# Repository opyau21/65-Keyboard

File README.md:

# 65% Keyboard Project Files
## Summary
  Creating a 65% Keyboard from scratch without any prior engineering knowledge.

## Next steps:
  * Write Software for ESP32 S3 Mini 1 and STM32

## To Do List:
* PCB: Finished, not yet tested
* Software (In Order)
  1. Keymaps
  2. OLED
  3. Fuel Gauge
  4. Magnetic Encoder
  5. Bluetooth
* Plate
* Foam
* Knob plastics
* Case
  1. Design
  2. Backweight
  3. OLED Screen
* Battery
* Program Software QMK/VIA

## BOM:
| Item # | Reference                                                                                                                                                                                                                                                                                                                                                                                                | Qty | Manufacturer                                                                               | Vendor            | Mfg Part #                                                                                                      | Value              | Description/Value                                                                | Package | Datasheet                                                                                            |
| ------ | -------------------------------------------------------------------------------------------------------------------------------------------------------------------------------------------------------------------------------------------------------------------------------------------------------------------------------------------------------------------------------------------------------- | --- | ------------------------------------------------------------------------------------------ | ----------------- | --------------------------------------------------------------------------------------------------------------- | ------------------ | -------------------------------------------------------------------------------- | ------- | ---------------------------------------------------------------------------------------------------- |
| 1      | C1, C11, C2, C3, C4, C5, C9                                                                                                                                                                                                                                                                                                                                                                              | 6   | Murata Electronics                                                                         | Mouser            | GRM155R71C103KA01J                                                                                              | 100nF              | Multilayer Ceramic Capacitors MLCC - SMD/SMT 0.01 uF 16 VDC 10% 0402 X7R         | 402     | ~                                                                                                    |
| 2      | C10,C15                                                                                                                                                                                                                                                                                                                                                                                                  | 2   | Murata Electronics                                                                         | Mouser            | GRM155R60J475ME47J                                                                                              | 4.7uF              | Multilayer Ceramic Capacitors MLCC - SMD/SMT 4.7 uF 6.3 VDC 20% 0402 X5R         | 402     | ~                                                                                                    |
| 3      | C8,C16                                                                                                                                                                                                                                                                                                                                                                                                   | 2   | Murata Electronics                                                                         | Mouser            | GRM1555C2A101GA01D                                                                                              | 10uF               | Multilayer Ceramic Capacitors MLCC - SMD/SMT 0402 10uF 4VDC 20% X6S AEC-Q200     | 402     | ~                                                                                                    |
| 4      | C14                                                                                                                                                                                                                                                                                                                                                                                                      | 1   | Murata Electronics                                                                         | Mouser            | GRM1555C2A101GA01D                                                                                              | 100pF              | Multilayer Ceramic Capacitors MLCC - SMD/SMT 100 pF 100 VDC 2% 0402 C0G (NP0)    | 402     | ~                                                                                                    |
| 5      | C17                                                                                                                                                                                                                                                                                                                                                                                                      | 1   | Murata Electronics                                                                         | Mouser            | GRM155R61A104KA01J                                                                                              | 0.1uF              | Multilayer Ceramic Capacitors MLCC - SMD/SMT 0.1 uF 10 VDC 10% 0402 X5R          | 402     | https://www.mouser.com/datasheet/2/281/1/GRM155R61A104KA01_02A-1983866.pdf                           |
| 6      | C6, C7                                                                                                                                                                                                                                                                                                                                                                                                   | 2   | Murata Electronics                                                                         | Mouser            | GXT155R60J105KE01D                                                                                              | 1uF                | Multilayer Ceramic Capacitors MLCC - SMD/SMT 0402 6.3VDC 1uF 10% X5R AEC-Q200    | 402     |                                                                                                      |
| 7      | C20,C21,C22,C23,C24,C25,C26,C27,C28,C29,C30,C31,C32,C33,C34,C35,C36,C37,C38,C39,C40,C41,C42,C43,C44,C45,C46,C47,C49,C50,C51,C52,C53,C54,C55,C56,C57,C58,C59,C60,C61,C62,C63,C64,C65,C66,C67,C68,C69,C70,C71,C72,C73,C74,C75,C76,C77,C78,C79,C80,C81,C82,C83,C84,C85,C86,C87                                                                                                                              | 67  | Murata Electronics                                                                         | Mouser            | GCM188R71C104KA37J                                                                                              | 0.1uF              | Multilayer Ceramic Capacitors MLCC - SMD/SMT 0.1 uF 16 VDC 10% 0603 X7R AEC-Q200 | 603     | ~                                                                                                    |
| 8      | D1,D2,D3,D4,D5,D6,D7,D8,D9,D10,D11,D12,D13,D14,D15,D16,D17,D18,D19,D20,D21,D22,D23,D24,D25,D26,D27,D28,D30,D31,D32,D33,D34,D35,D36,D37,D38,D39,D40,D41,D42,D43,D44,D45,D46,D47,D48,D49,D50,D51,D52,D53,D54,D55,D56,D57,D58,D59,D60,D61,D62,D63,D64,D65,D66,D67,D68                                                                                                                                       | 67  |                                                                                            | Adafruit          |                                                                                                                 | D_Small            | Adafruit Accessories 1N4148 SMT SOD-123 Diodes - 100 Pack                        |         | ~                                                                                                    |
| 9      | J1                                                                                                                                                                                                                                                                                                                                                                                                       | 1   |                                                                                            | AliExpress        |                                                                                                                 | Conn_01x02         |                                                                                  |         | ~                                                                                                    |
| 10     | J2                                                                                                                                                                                                                                                                                                                                                                                                       | 1   |                                                                                            | AliExpress        |                                                                                                                 | Conn_01x04         |                                                                                  |         | ~                                                                                                    |
| 11     | J3                                                                                                                                                                                                                                                                                                                                                                                                       | 1   |                                                                                            | AliExpress        |                                                                                                                 | Conn_01x07         |                                                                                  |         | ~                                                                                                    |
| 12     | LED1,LED2,LED3,LED4,LED5,LED6,LED7,LED8,LED9,LED10,LED11,LED12,LED13,LED14,LED15,LED16,LED17,LED18,LED19,LED20,LED21,LED22,LED23,LED24,LED25,LED26,LED27,LED28,LED30,LED31,LED32,LED33,LED34,LED35,LED36,LED37,LED38,LED39,LED40,LED41,LED42,LED43,LED44,LED45,LED46,LED47,LED48,LED49,LED50,LED51,LED52,LED53,LED54,LED55,LED56,LED57,LED58,LED59,LED60,LED61,LED62,LED63,LED64,LED65,LED66,LED67,LED68 | 67  |                                                                                            | AliExpress        |                                                                                                                 | LED_SK6812MINI     |                                                                                  |         | https://cdn-shop.adafruit.com/product-files/2686/SK6812MINI_REV.01-1-2.pdf                           |
| 13     | R1, R11, R12, R17, R3, R5                                                                                                                                                                                                                                                                                                                                                                                | 6   | YAGEO                                                                                      | Mouser            | RC0402JR-7D10KL                                                                                                 | 10k                | Thick Film Resistors - SMD 10 kOhms 62.5 mW 0402 5%                              | 402     | ~                                                                                                    |
| 14     | R6,R7,R8,R9,R10                                                                                                                                                                                                                                                                                                                                                                                          | 5   | YAGEO                                                                                      | Mouser            | [RC0402FR-7D4K7L](https://www.mouser.com/ProductDetail/YAGEO/RC0402FR-7D4K7L?qs=F5EMLAvA7ID7%2FFIVczkChg%3D%3D) | 4.7k               | Thick Film Resistors - SMD 4.7 kOhms 62.5 mW 0402 1%                             | 402     | ~                                                                                                    |
| 15     | R15                                                                                                                                                                                                                                                                                                                                                                                                      | 1   | YAGEO                                                                                      | Mouser            |                                                                                                                 | 1k                 |                                                                                  | 402     | ~                                                                                                    |
| 16     | R16                                                                                                                                                                                                                                                                                                                                                                                                      | 1   | YAGEO                                                                                      | Mouser            |                                                                                                                 | 750                |                                                                                  | 402     | ~                                                                                                    |
| 17     | S1,S2,S3,S4,S5,S6,S7,S8,S9,S10,S11,S12,S13,S14,S16,S17,S18,S19,S20,S21,S22,S23,S24,S25,S26,S27,S31,S32,S33,S34,S35,S36,S37,S38,S39,S40,S41,S42,S43,S44,S45,S46,S47,S48,S49,S50,S51,S52,S53,S54,S56,S57,S61,S64,S65,S66,S71,S72                                                                                                                                                                           | 58  |                                                                                            | Cannonkeys        |                                                                                                                 | Keyswitch          | Kailh MX Hotswap Sockets - 110 Pack                                              |         | ~                                                                                                    |
| 18     | S15,S28                                                                                                                                                                                                                                                                                                                                                                                                  | 2   |                                                                                            |                   |                                                                                                                 | Keyswitch          |                                                                                  |         | ~                                                                                                    |
| 19     | S30,S55                                                                                                                                                                                                                                                                                                                                                                                                  | 2   |                                                                                            |                   |                                                                                                                 | Keyswitch          |                                                                                  |         | ~                                                                                                    |
| 20     | S58,S59,S60,S62,S63                                                                                                                                                                                                                                                                                                                                                                                      | 5   |                                                                                            |                   |                                                                                                                 | Keyswitch          |                                                                                  |         | ~                                                                                                    |
| 21     | S67                                                                                                                                                                                                                                                                                                                                                                                                      | 1   |                                                                                            | Divinikey         |                                                                                                                 | MX_stab            | TX Stabilizers                                                                   |         |                                                                                                      |
| 22     | S68,S69                                                                                                                                                                                                                                                                                                                                                                                                  | 2   |                                                                                            |                   |                                                                                                                 | MX_stab            |                                                                                  |         |                                                                                                      |
| 23     | S70                                                                                                                                                                                                                                                                                                                                                                                                      | 1   |                                                                                            |                   |                                                                                                                 | MX_stab            |                                                                                  |         |                                                                                                      |
| 24     | SW1,SW2                                                                                                                                                                                                                                                                                                                                                                                                  | 2   | E-Switch                                                                                   | Mouser            | TL3342F450QG                                                                                                    | SW_Push            | Tactile Switches 50mA 12VDC Silver Gull Wing                                     |         | ~                                                                                                    |
| 25     | U1                                                                                                                                                                                                                                                                                                                                                                                                       | 1   | [Analog Devices / Maxim Integrated](https://www.mouser.com/manufacturer/maxim-integrated/) | Mouser            | MAX17048G+T10                                                                                                   | MAX17048G_T10      | Battery Management 3 A 1-Cell/2-Cell Fuel Gauge with ModelGauge                  |         |                                                                                                      |
| 26     | U2                                                                                                                                                                                                                                                                                                                                                                                                       | 1   | Semtech                                                                                    | Mouser            | SRV05-4.TCT                                                                                                     | SRV05-4            | ESD Protection Diodes / TVS Diodes RAILCLAMP 4-LINE 5V 3K LFREE                  |         | http://www.onsemi.com/pub/Collateral/SRV05-4-D.PDF                                                   |
| 27     | U3                                                                                                                                                                                                                                                                                                                                                                                                       | 1   | Azoteq                                                                                     | Mouser            | IQS6243200DNR                                                                                                   | IQS624-3200-DNR    | Board Mount Motion & Position Sensors 2 x Capacitive, Hall rotation              |         |                                                                                                      |
| 28     | U4                                                                                                                                                                                                                                                                                                                                                                                                       | 1   | EspressIf                                                                                  | Mouser            | ESP32-S3-MINI-1-N8                                                                                              | ESP32-S3-MINI-1-N8 | Multiprotocol Modules SMD module, ESP32-S3FN8, 8 MB SPI flash, PCB antenna       |         | https://www.espressif.com/sites/default/files/documentation/esp32-s3-mini-1_mini-1u_datasheet_en.pdf |
| 29     | U5                                                                                                                                                                                                                                                                                                                                                                                                       | 1   |                                                                                            | Mouser            | BQ25185DLHR                                                                                                     | BQ25185DLHR        |                                                                                  |         |                                                                                                      |
| 30     | U6                                                                                                                                                                                                                                                                                                                                                                                                       | 1   | STMicroelectronics                                                                         | Mouser            | STM32F103RET6TR                                                                                                 | STM32F103RETx      | ARM Microcontrollers - MCU 32BIT Cortex M3 H/D Performance LINE                  |         | https://www.st.com/resource/en/datasheet/stm32f103re.pdf                                             |
| 31     | U7                                                                                                                                                                                                                                                                                                                                                                                                       | 1   | UMW                                                                                        | Digikey           | AMS1117-3.3                                                                                                     | AMS1117-3.3        | 3.3V LDO Regulator                                                               |         |                                                                                                      |
| 32     | F1                                                                                                                                                                                                                                                                                                                                                                                                       | 1   | Bourns                                                                                     | Mouser            | MF-FSMF050X-2                                                                                                   | MF-FSMF050X-2      | Resettable Fuses - PPTC 6V .5A-HD 40A MAX                                        |         |                                                                                                      |
| 33     |                                                                                                                                                                                                                                                                                                                                                                                                          | 1   |                                                                                            | Amazon/AliExpress |                                                                                                                 | 5000 mah           | 5000 mah Lithium Ion Recharable Battery                                          |         |                                                                                                      |
| 34     |                                                                                                                                                                                                                                                                                                                                                                                                          | 1   |                                                                                            | AliExpress        |                                                                                                                 | 01x07 JST PH Wire  | 01x07 JST PH Wire                                                                |         |                                                                                                      |
| 35     |                                                                                                                                                                                                                                                                                                                                                                                                          | 1   | aio3                                                                                       | Cannonkeys        |                                                                                                                 |                    | Unified Daughterboard                                                            |         |                                                                                                      |
| 36     |                                                                                                                                                                                                                                                                                                                                                                                                          | 1   | Waveshare                                                                                  | Amazon            |                                                                                                                 | 128 x 128          | 1.5 inch 128 x 128 RGB OLED Screen                                               |         |                                                                                                      |
| 37     |                                                                                                                                                                                                                                                                                                                                                                                                          | 1   | Logitech                                                                                   | AliExpress        |                                                                                                                 |                    | Logitech MX Master 3s Side Scroll Component                                      |         |                                                                                                      |

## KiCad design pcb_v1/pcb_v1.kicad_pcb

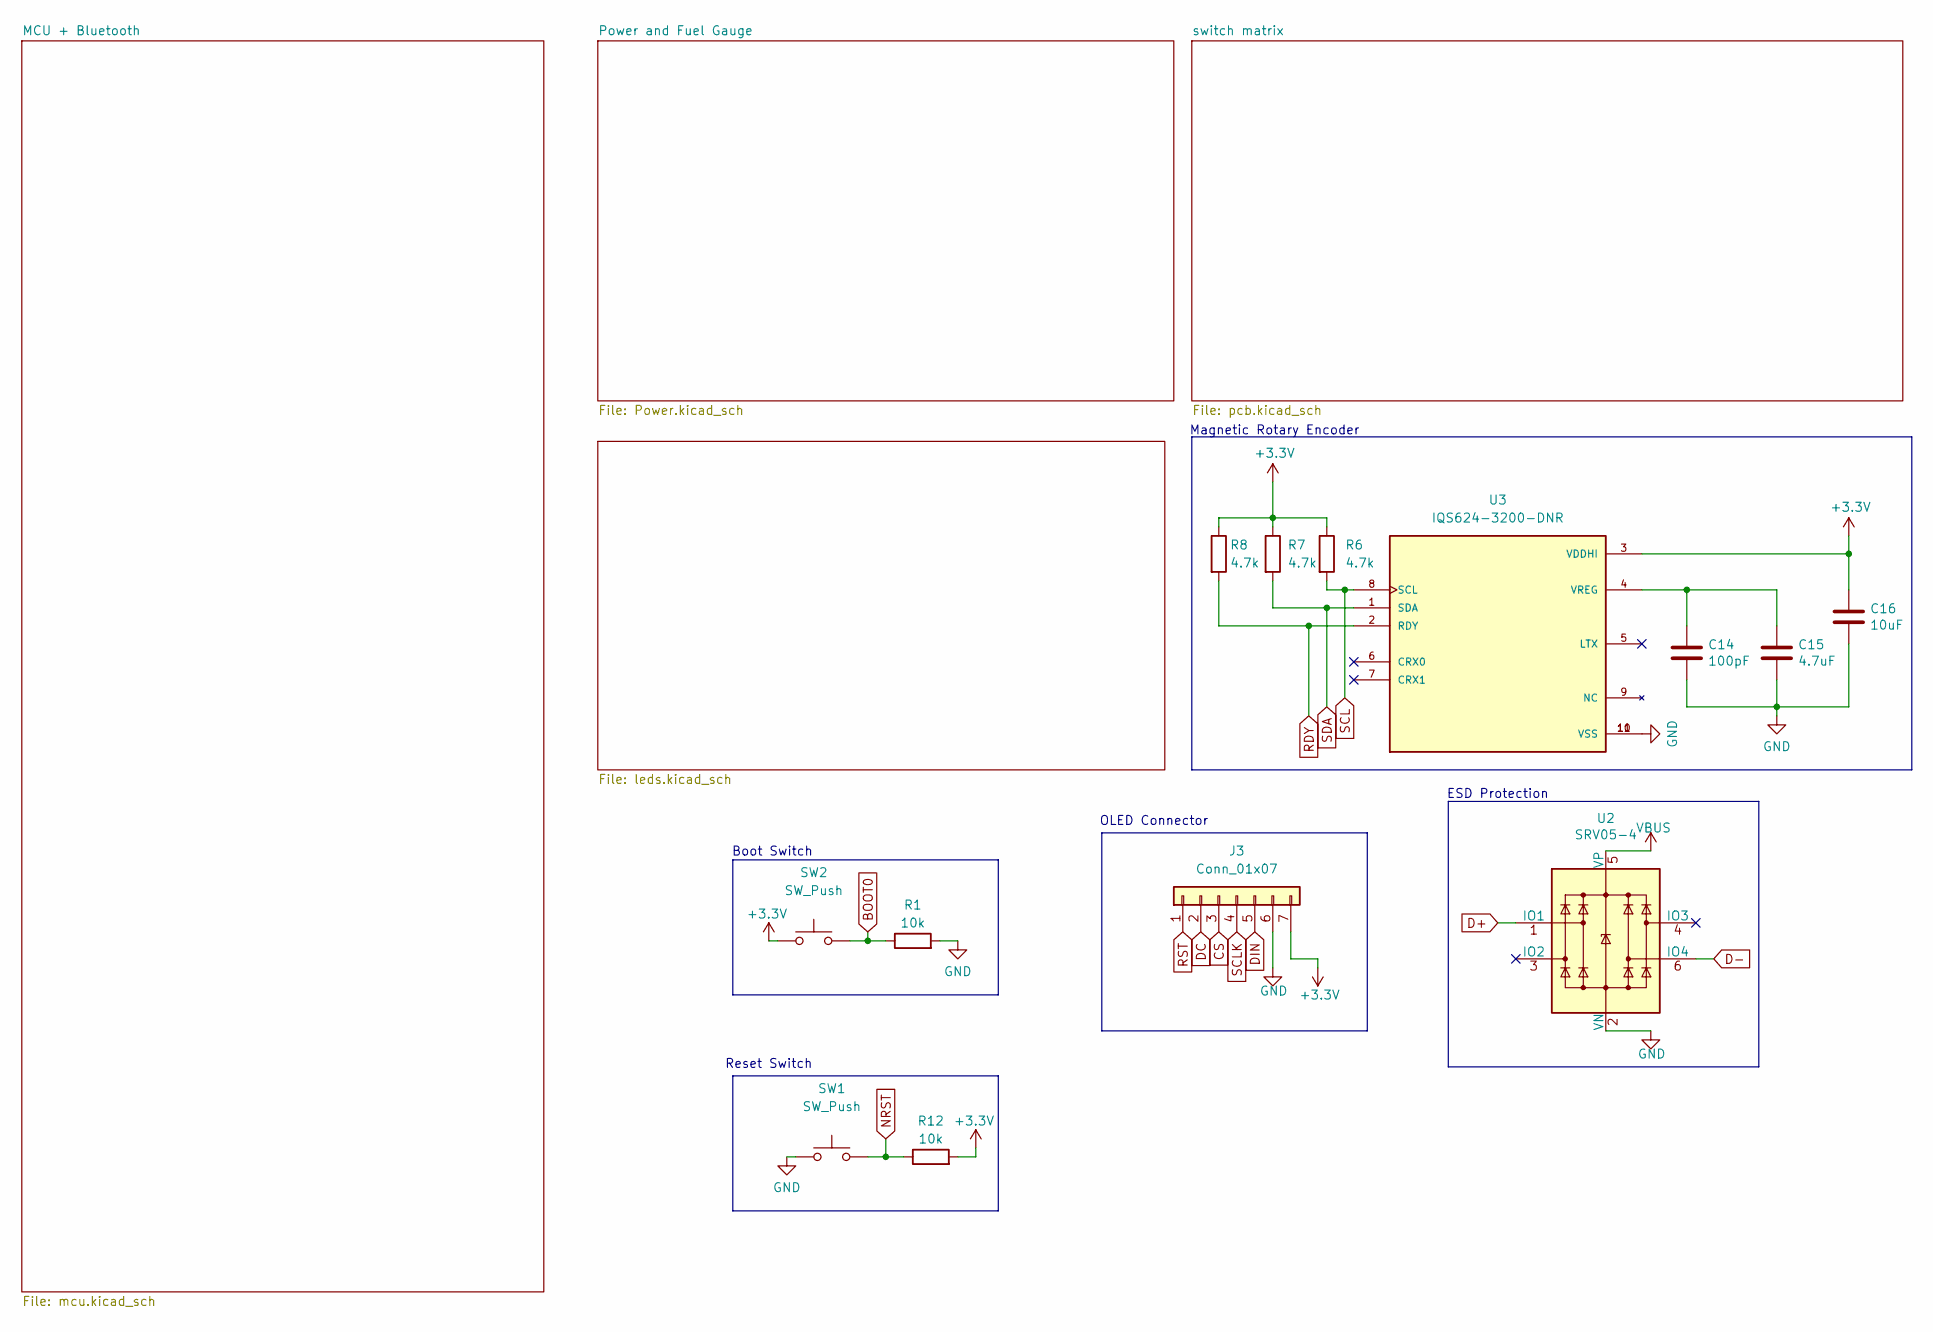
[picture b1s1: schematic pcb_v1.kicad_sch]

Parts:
C14: 100pF; CAPC1005X55N; LCSC Part # C49678
C15: 4.7uF; CAPC1005X55N; LCSC Part # C49678
C16: 10uF; CAPC1005X55N; LCSC Part # C49678
J3: Conn_01x07; JST_PH_S7B-PH-SM4-TB_1x07-1MP_P2.00mm_Horizontal
R1, R12: 10k; RESC1005X40N
R6, R7, R8: 4.7k; RESC1005X40N
SW1, SW2: SW_Push; Button_TL3342
U2: SRV05-4; SOT-23-6; LCSC Part # C85364
U3: IQS624-3200-DNR; SON50P300X300X80-11N; PARTREV 2.04

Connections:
+3.3V: C16.1, J3.7, R6.1, R7.1, R8.1, R12.2, SW2.1, U3.3 (VDDHI); also elsewhere on the board
BOOT0: R1.1, SW2.2; also elsewhere on the board
CS: J3.3; also elsewhere on the board
D+: U2.1 (IO1); also elsewhere on the board
D-: U2.6 (IO4); also elsewhere on the board
DC: J3.2; also elsewhere on the board
DIN: J3.5; also elsewhere on the board
GND: C14.2, C15.2, C16.2, J3.6, R1.2, SW1.1, U2.2 (VN), U3.10 (VSS), U3.11 (VSS); also elsewhere on the board
NRST: R12.1, SW1.2; also elsewhere on the board
unnamed: C14.1, C15.1, U3.4 (VREG)
RDY: R8.2, U3.2 (RDY); also elsewhere on the board
RST: J3.1; also elsewhere on the board
SCL: R6.2, U3.8 (SCL); also elsewhere on the board
SCLK: J3.4; also elsewhere on the board
SDA: R7.2, U3.1 (SDA); also elsewhere on the board
VBUS: U2.5 (VP); also elsewhere on the board

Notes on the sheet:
OLED Connector
Boot Switch
ESD Protection
Magnetic Rotary Encoder
Reset Switch

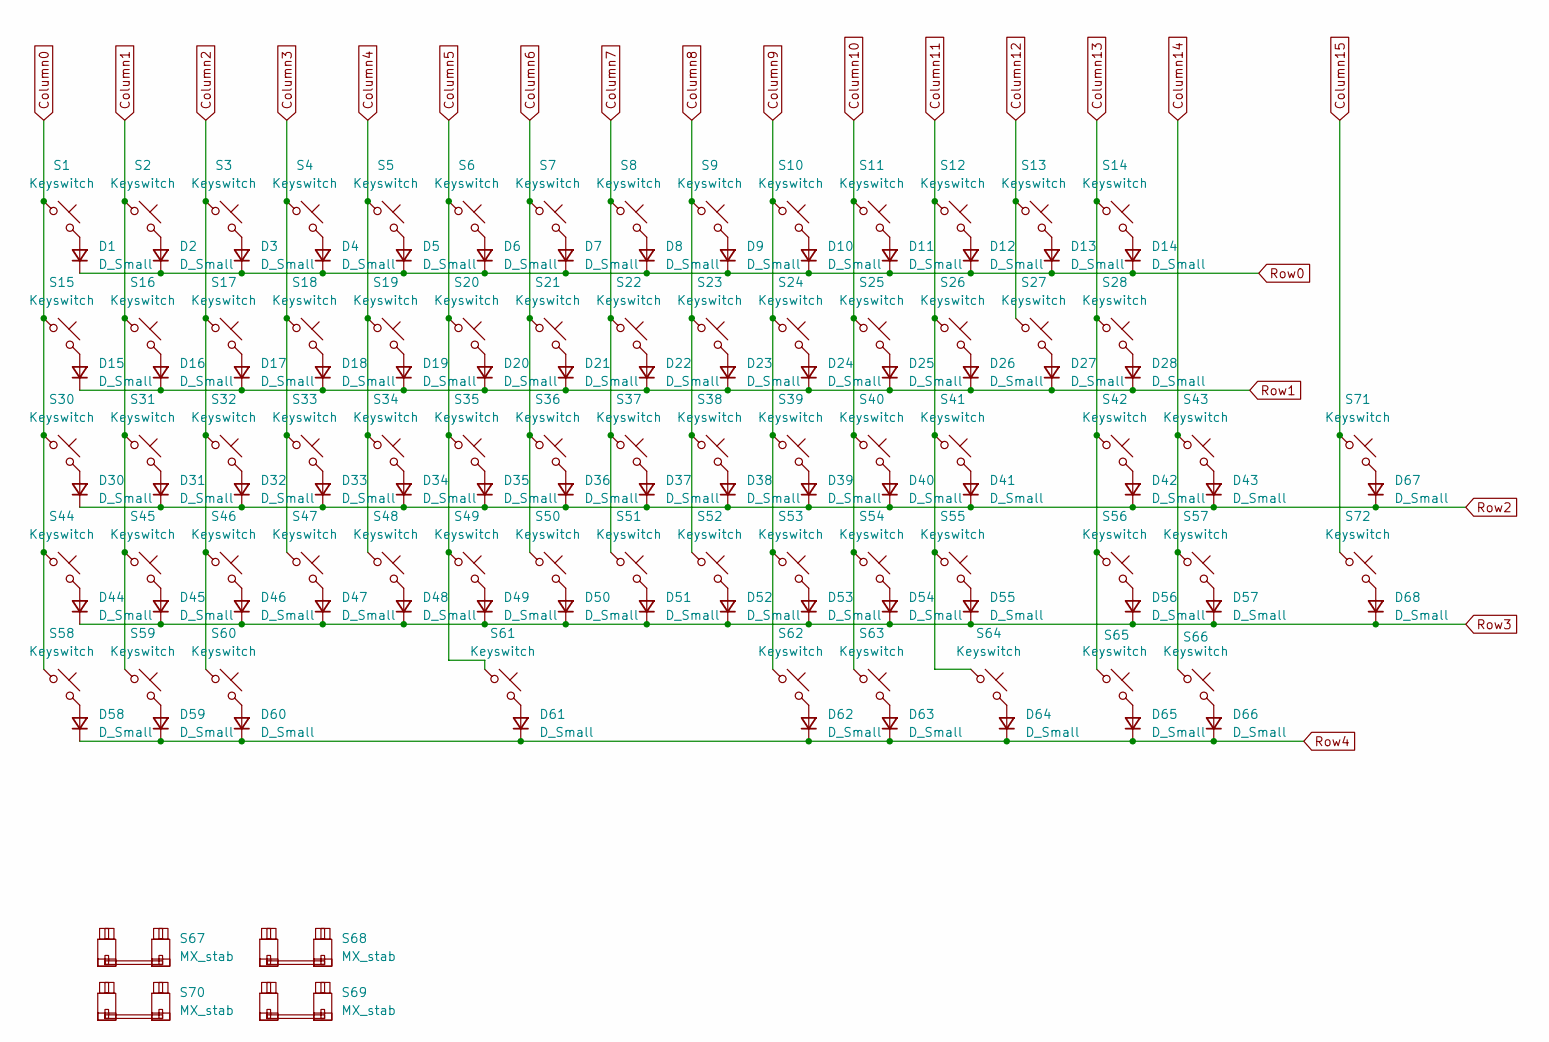
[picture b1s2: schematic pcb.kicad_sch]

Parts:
D1, D2, D3, D4, D5, D6, D7, D8, D9, D10, D11, D12, D13, D14, D15, D16, D17, D18, D19, D20, D21, D22, D23, D24, D25, D26, D27, D28, D30, D31, D32, D33, D34, D35, D36, D37, D38, D39, D40, D41, D42, D43, D44, D45, D46, D47, D48, D49, D50, D51, D52, D53, D54, D55, D56, D57, D58, D59, D60, D61, D62, D63, D64, D65, D66, D67, D68: D_Small; Diode_SOD-123
S1, S2, S3, S4, S5, S6, S7, S8, S9, S10, S11, S12, S13, S14, S16, S17, S18, S19, S20, S21, S22, S23, S24, S25, S26, S27, S31, S32, S33, S34, S35, S36, S37, S38, S39, S40, S41, S42, S43, S44, S45, S46, S47, S48, S49, S50, S51, S52, S53, S54, S56, S57, S61, S64, S65, S66, S71, S72: Keyswitch; SW_MX_HS_CPG151101S11_1u
S15, S28: Keyswitch; SW_MX_HS_CPG151101S11_1.5u
S30, S55: Keyswitch; SW_MX_HS_CPG151101S11_1.75u
S58, S59, S60, S62, S63: Keyswitch; SW_MX_HS_CPG151101S11_1.25u
S67: MX_stab; STAB_MX_P_2u
S68, S69: MX_stab; STAB_MX_2.25u
S70: MX_stab; STAB_MX_P_6.25u

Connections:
Column0: S1.1, S15.1, S30.1, S44.1, S58.1; also elsewhere on the board
Column1: S2.1, S16.1, S31.1, S45.1, S59.1; also elsewhere on the board
Column2: S3.1, S17.1, S32.1, S46.1, S60.1; also elsewhere on the board
Column3: S4.1, S18.1, S33.1, S47.1; also elsewhere on the board
Column4: S5.1, S19.1, S34.1, S48.1; also elsewhere on the board
Column5: S6.1, S20.1, S35.1, S49.1, S61.1; also elsewhere on the board
Column6: S7.1, S21.1, S36.1, S50.1; also elsewhere on the board
Column7: S8.1, S22.1, S37.1, S51.1; also elsewhere on the board
Column8: S9.1, S23.1, S38.1, S52.1; also elsewhere on the board
Column9: S10.1, S24.1, S39.1, S53.1, S62.1; also elsewhere on the board
Column10: S11.1, S25.1, S40.1, S54.1, S63.1; also elsewhere on the board
Column11: S12.1, S26.1, S41.1, S55.1, S64.1; also elsewhere on the board
Column12: S13.1, S27.1; also elsewhere on the board
Column13: S14.1, S28.1, S42.1, S56.1, S65.1; also elsewhere on the board
Column14: S43.1, S57.1, S66.1; also elsewhere on the board
Column15: S71.1, S72.1; also elsewhere on the board
unnamed: D1.2 (A), S1.2
unnamed: D2.2 (A), S2.2
unnamed: D3.2 (A), S3.2
unnamed: D4.2 (A), S4.2
unnamed: D5.2 (A), S5.2
unnamed: D6.2 (A), S6.2
unnamed: D7.2 (A), S7.2
unnamed: D8.2 (A), S8.2
unnamed: D9.2 (A), S9.2
unnamed: D10.2 (A), S10.2
unnamed: D11.2 (A), S11.2
unnamed: D12.2 (A), S12.2
unnamed: D13.2 (A), S13.2
unnamed: D14.2 (A), S14.2
unnamed: D15.2 (A), S15.2
unnamed: D16.2 (A), S16.2
unnamed: D17.2 (A), S17.2
unnamed: D18.2 (A), S18.2
unnamed: D19.2 (A), S19.2
unnamed: D20.2 (A), S20.2
unnamed: D21.2 (A), S21.2
unnamed: D22.2 (A), S22.2
unnamed: D23.2 (A), S23.2
unnamed: D24.2 (A), S24.2
unnamed: D25.2 (A), S25.2
unnamed: D26.2 (A), S26.2
unnamed: D27.2 (A), S27.2
unnamed: D28.2 (A), S28.2
unnamed: D30.2 (A), S30.2
unnamed: D31.2 (A), S31.2
unnamed: D32.2 (A), S32.2
unnamed: D33.2 (A), S33.2
unnamed: D34.2 (A), S34.2
unnamed: D35.2 (A), S35.2
unnamed: D36.2 (A), S36.2
unnamed: D37.2 (A), S37.2
unnamed: D38.2 (A), S38.2
unnamed: D39.2 (A), S39.2
unnamed: D40.2 (A), S40.2
unnamed: D41.2 (A), S41.2
unnamed: D42.2 (A), S42.2
unnamed: D43.2 (A), S43.2
unnamed: D44.2 (A), S44.2
unnamed: D45.2 (A), S45.2
unnamed: D46.2 (A), S46.2
unnamed: D47.2 (A), S47.2
unnamed: D48.2 (A), S48.2
unnamed: D49.2 (A), S49.2
unnamed: D50.2 (A), S50.2
unnamed: D51.2 (A), S51.2
unnamed: D52.2 (A), S52.2
unnamed: D53.2 (A), S53.2
unnamed: D54.2 (A), S54.2
unnamed: D55.2 (A), S55.2
unnamed: D56.2 (A), S56.2
unnamed: D57.2 (A), S57.2
unnamed: D58.2 (A), S58.2
unnamed: D59.2 (A), S59.2
unnamed: D60.2 (A), S60.2
unnamed: D61.2 (A), S61.2
unnamed: D62.2 (A), S62.2
unnamed: D63.2 (A), S63.2
unnamed: D64.2 (A), S64.2
unnamed: D65.2 (A), S65.2
unnamed: D66.2 (A), S66.2
unnamed: D67.2 (A), S71.2
unnamed: D68.2 (A), S72.2
Row0: D1.1 (K), D2.1 (K), D3.1 (K), D4.1 (K), D5.1 (K), D6.1 (K), D7.1 (K), D8.1 (K), D9.1 (K), D10.1 (K), D11.1 (K), D12.1 (K), D13.1 (K), D14.1 (K); also elsewhere on the board
Row1: D15.1 (K), D16.1 (K), D17.1 (K), D18.1 (K), D19.1 (K), D20.1 (K), D21.1 (K), D22.1 (K), D23.1 (K), D24.1 (K), D25.1 (K), D26.1 (K), D27.1 (K), D28.1 (K); also elsewhere on the board
Row2: D30.1 (K), D31.1 (K), D32.1 (K), D33.1 (K), D34.1 (K), D35.1 (K), D36.1 (K), D37.1 (K), D38.1 (K), D39.1 (K), D40.1 (K), D41.1 (K), D42.1 (K), D43.1 (K), D67.1 (K); also elsewhere on the board
Row3: D44.1 (K), D45.1 (K), D46.1 (K), D47.1 (K), D48.1 (K), D49.1 (K), D50.1 (K), D51.1 (K), D52.1 (K), D53.1 (K), D54.1 (K), D55.1 (K), D56.1 (K), D57.1 (K), D68.1 (K); also elsewhere on the board
Row4: D58.1 (K), D59.1 (K), D60.1 (K), D61.1 (K), D62.1 (K), D63.1 (K), D64.1 (K), D65.1 (K), D66.1 (K); also elsewhere on the board

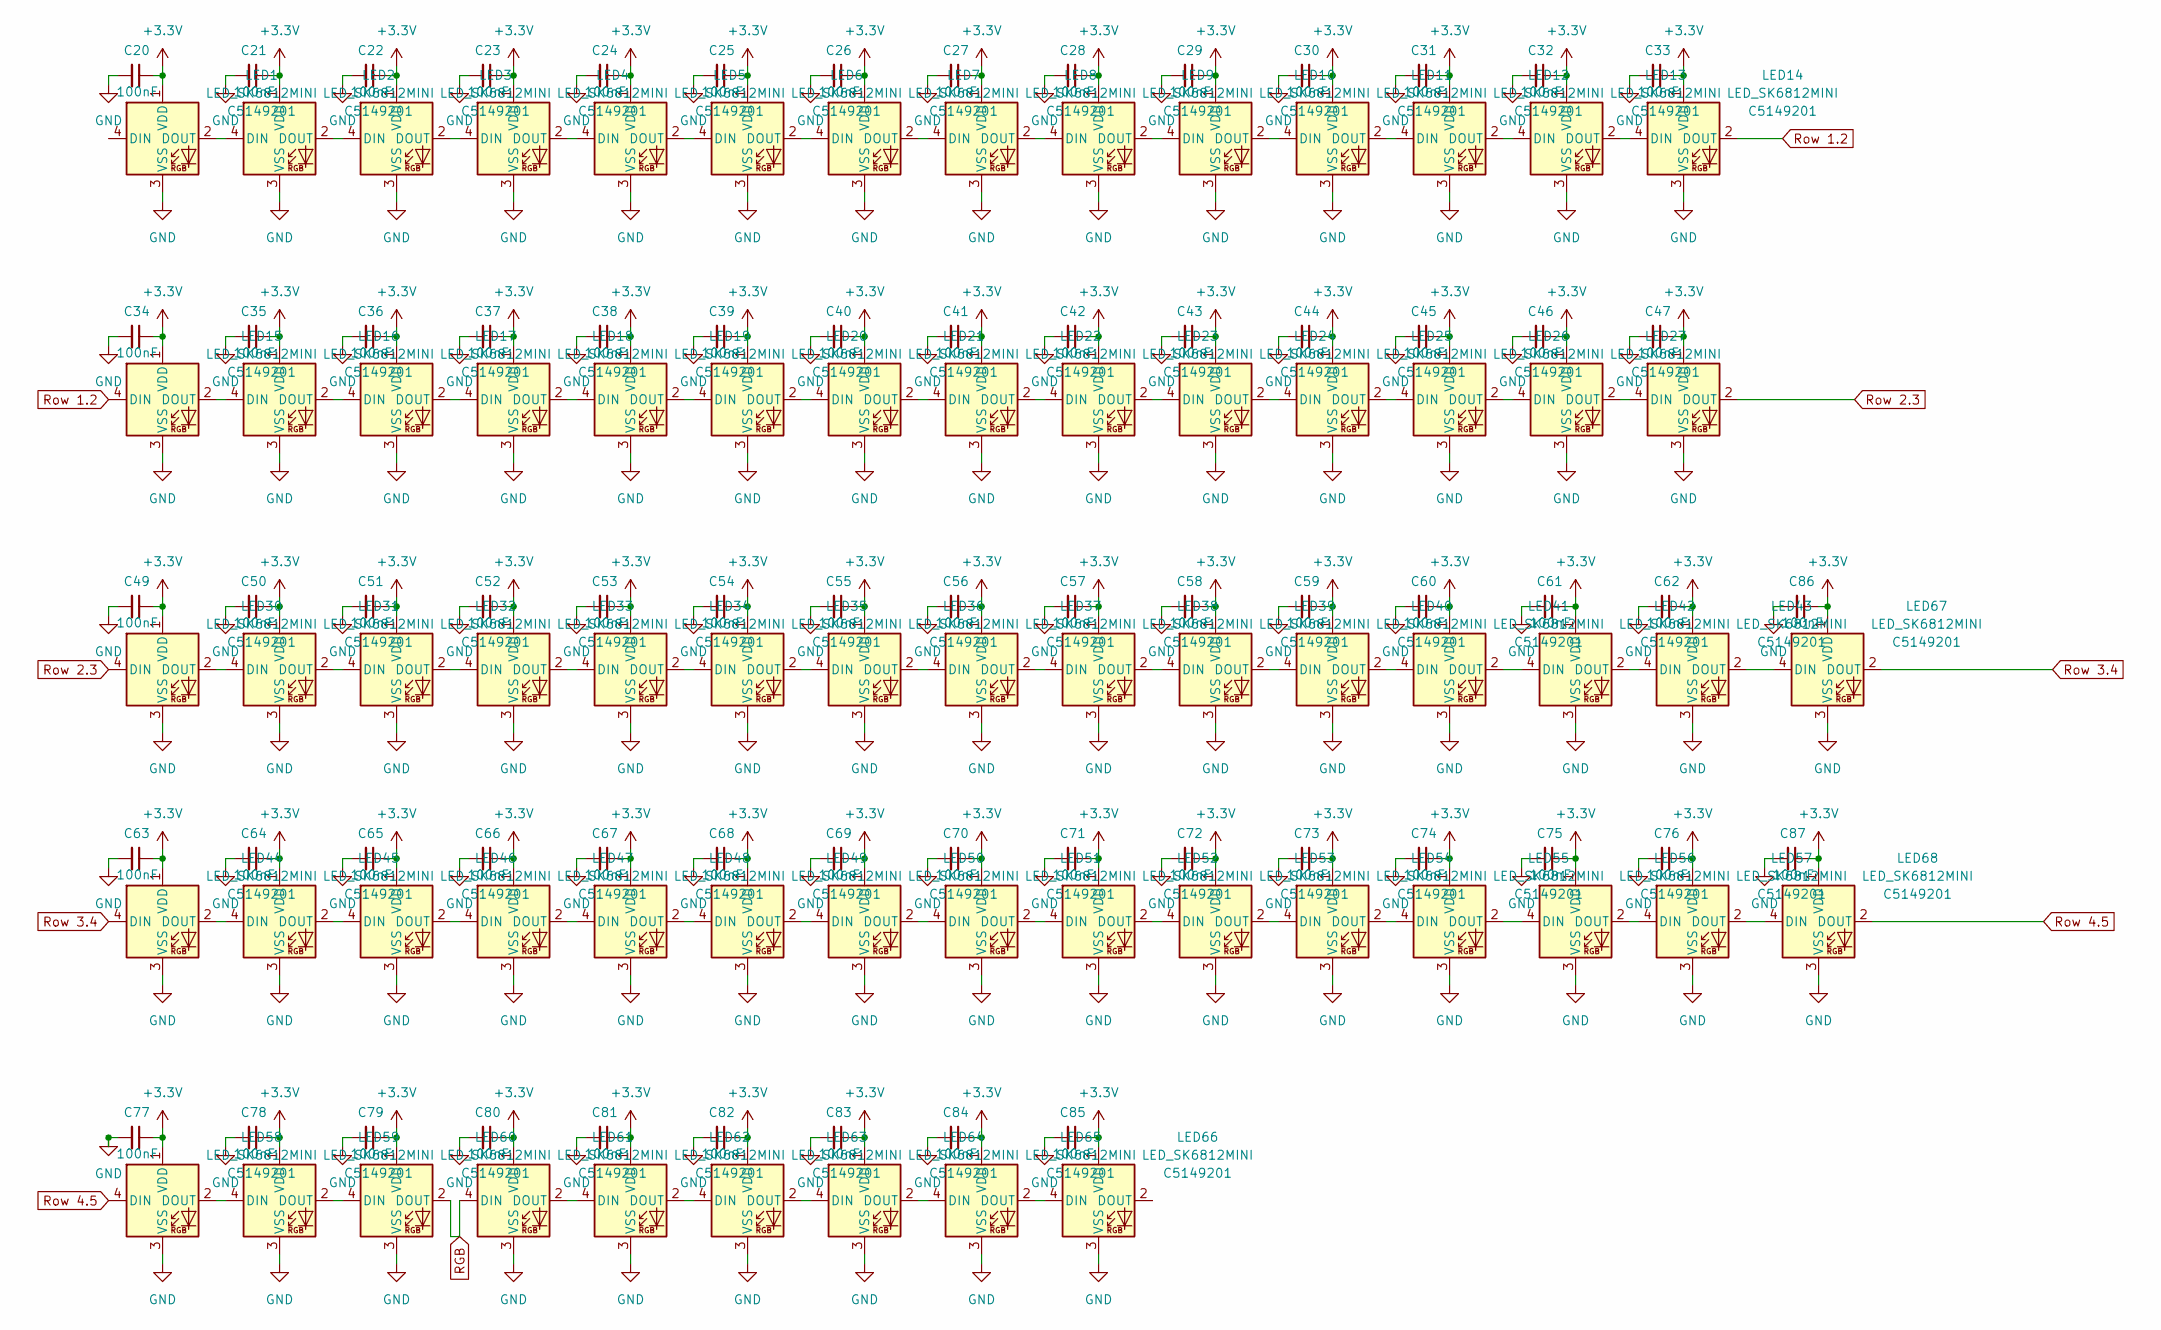
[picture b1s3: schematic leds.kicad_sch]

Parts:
C20, C21, C22, C23, C24, C25, C26, C27, C28, C29, C30, C31, C32, C33, C34, C35, C36, C37, C38, C39, C40, C41, C42, C43, C44, C45, C46, C47, C49, C50, C51, C52, C53, C54, C55, C56, C57, C58, C59, C60, C61, C62, C63, C64, C65, C66, C67, C68, C69, C70, C71, C72, C73, C74, C75, C76, C77, C78, C79, C80, C81, C82, C83, C84, C85, C86, C87: 100nF; CAPC1608X90N
LED1, LED2, LED3, LED4, LED5, LED6, LED7, LED8, LED9, LED10, LED11, LED12, LED13, LED14, LED15, LED16, LED17, LED18, LED19, LED20, LED21, LED22, LED23, LED24, LED25, LED26, LED27, LED28, LED30, LED31, LED32, LED33, LED34, LED35, LED36, LED37, LED38, LED39, LED40, LED41, LED42, LED43, LED44, LED45, LED46, LED47, LED48, LED49, LED50, LED51, LED52, LED53, LED54, LED55, LED56, LED57, LED58, LED59, LED60, LED61, LED62, LED63, LED64, LED65, LED66, LED67, LED68: LED_SK6812MINI; LCSC C5149201

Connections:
+3.3V: C20.1, C21.1, C22.1, C23.1, C24.1, C25.1, C26.1, C27.1, C28.1, C29.1, C30.1, C31.1, C32.1, C33.1, C34.1, C35.1, C36.1, C37.1, C38.1, C39.1, C40.1, C41.1, C42.1, C43.1, C44.1, C45.1, C46.1, C47.1, C49.1, C50.1, C51.1, C52.1, C53.1, C54.1, C55.1, C56.1, C57.1, C58.1, C59.1, C60.1, C61.1, C62.1, C63.1, C64.1, C65.1, C66.1, C67.1, C68.1, C69.1, C70.1, C71.1, C72.1, C73.1, C74.1, C75.1, C76.1, C77.1, C78.1, C79.1, C80.1, C81.1, C82.1, C83.1, C84.1, C85.1, C86.1, C87.1, LED1.1 (VDD), LED2.1 (VDD), LED3.1 (VDD), LED4.1 (VDD), LED5.1 (VDD), LED6.1 (VDD), LED7.1 (VDD), LED8.1 (VDD), LED9.1 (VDD), LED10.1 (VDD), LED11.1 (VDD), LED12.1 (VDD), LED13.1 (VDD), LED14.1 (VDD), LED15.1 (VDD), LED16.1 (VDD), LED17.1 (VDD), LED18.1 (VDD), LED19.1 (VDD), LED20.1 (VDD), LED21.1 (VDD), LED22.1 (VDD), LED23.1 (VDD), LED24.1 (VDD), LED25.1 (VDD), LED26.1 (VDD), LED27.1 (VDD), LED28.1 (VDD), LED30.1 (VDD), LED31.1 (VDD), LED32.1 (VDD), LED33.1 (VDD), LED34.1 (VDD), LED35.1 (VDD), LED36.1 (VDD), LED37.1 (VDD), LED38.1 (VDD), LED39.1 (VDD), LED40.1 (VDD), LED41.1 (VDD), LED42.1 (VDD), LED43.1 (VDD), LED44.1 (VDD), LED45.1 (VDD), LED46.1 (VDD), LED47.1 (VDD), LED48.1 (VDD), LED49.1 (VDD), LED50.1 (VDD), LED51.1 (VDD), LED52.1 (VDD), LED53.1 (VDD), LED54.1 (VDD), LED55.1 (VDD), LED56.1 (VDD), LED57.1 (VDD), LED58.1 (VDD), LED59.1 (VDD), LED60.1 (VDD), LED61.1 (VDD), LED62.1 (VDD), LED63.1 (VDD), LED64.1 (VDD), LED65.1 (VDD), LED66.1 (VDD), LED67.1 (VDD), LED68.1 (VDD); also elsewhere on the board
GND: C20.2, C21.2, C22.2, C23.2, C24.2, C25.2, C26.2, C27.2, C28.2, C29.2, C30.2, C31.2, C32.2, C33.2, C34.2, C35.2, C36.2, C37.2, C38.2, C39.2, C40.2, C41.2, C42.2, C43.2, C44.2, C45.2, C46.2, C47.2, C49.2, C50.2, C51.2, C52.2, C53.2, C54.2, C55.2, C56.2, C57.2, C58.2, C59.2, C60.2, C61.2, C62.2, C63.2, C64.2, C65.2, C66.2, C67.2, C68.2, C69.2, C70.2, C71.2, C72.2, C73.2, C74.2, C75.2, C76.2, C77.2, C78.2, C79.2, C80.2, C81.2, C82.2, C83.2, C84.2, C85.2, C86.2, C87.2, LED1.3 (VSS), LED2.3 (VSS), LED3.3 (VSS), LED4.3 (VSS), LED5.3 (VSS), LED6.3 (VSS), LED7.3 (VSS), LED8.3 (VSS), LED9.3 (VSS), LED10.3 (VSS), LED11.3 (VSS), LED12.3 (VSS), LED13.3 (VSS), LED14.3 (VSS), LED15.3 (VSS), LED16.3 (VSS), LED17.3 (VSS), LED18.3 (VSS), LED19.3 (VSS), LED20.3 (VSS), LED21.3 (VSS), LED22.3 (VSS), LED23.3 (VSS), LED24.3 (VSS), LED25.3 (VSS), LED26.3 (VSS), LED27.3 (VSS), LED28.3 (VSS), LED30.3 (VSS), LED31.3 (VSS), LED32.3 (VSS), LED33.3 (VSS), LED34.3 (VSS), LED35.3 (VSS), LED36.3 (VSS), LED37.3 (VSS), LED38.3 (VSS), LED39.3 (VSS), LED40.3 (VSS), LED41.3 (VSS), LED42.3 (VSS), LED43.3 (VSS), LED44.3 (VSS), LED45.3 (VSS), LED46.3 (VSS), LED47.3 (VSS), LED48.3 (VSS), LED49.3 (VSS), LED50.3 (VSS), LED51.3 (VSS), LED52.3 (VSS), LED53.3 (VSS), LED54.3 (VSS), LED55.3 (VSS), LED56.3 (VSS), LED57.3 (VSS), LED58.3 (VSS), LED59.3 (VSS), LED60.3 (VSS), LED61.3 (VSS), LED62.3 (VSS), LED63.3 (VSS), LED64.3 (VSS), LED65.3 (VSS), LED66.3 (VSS), LED67.3 (VSS), LED68.3 (VSS); also elsewhere on the board
unnamed: LED1.2 (DOUT), LED2.4 (DIN)
unnamed: LED2.2 (DOUT), LED3.4 (DIN)
unnamed: LED3.2 (DOUT), LED4.4 (DIN)
unnamed: LED4.2 (DOUT), LED5.4 (DIN)
unnamed: LED5.2 (DOUT), LED6.4 (DIN)
unnamed: LED6.2 (DOUT), LED7.4 (DIN)
unnamed: LED7.2 (DOUT), LED8.4 (DIN)
unnamed: LED8.2 (DOUT), LED9.4 (DIN)
unnamed: LED9.2 (DOUT), LED10.4 (DIN)
unnamed: LED10.2 (DOUT), LED11.4 (DIN)
unnamed: LED11.2 (DOUT), LED12.4 (DIN)
unnamed: LED12.2 (DOUT), LED13.4 (DIN)
unnamed: LED13.2 (DOUT), LED14.4 (DIN)
unnamed: LED15.2 (DOUT), LED16.4 (DIN)
unnamed: LED16.2 (DOUT), LED17.4 (DIN)
unnamed: LED17.2 (DOUT), LED18.4 (DIN)
unnamed: LED18.2 (DOUT), LED19.4 (DIN)
unnamed: LED19.2 (DOUT), LED20.4 (DIN)
unnamed: LED20.2 (DOUT), LED21.4 (DIN)
unnamed: LED21.2 (DOUT), LED22.4 (DIN)
unnamed: LED22.2 (DOUT), LED23.4 (DIN)
unnamed: LED23.2 (DOUT), LED24.4 (DIN)
unnamed: LED24.2 (DOUT), LED25.4 (DIN)
unnamed: LED25.2 (DOUT), LED26.4 (DIN)
unnamed: LED26.2 (DOUT), LED27.4 (DIN)
unnamed: LED27.2 (DOUT), LED28.4 (DIN)
unnamed: LED30.2 (DOUT), LED31.4 (DIN)
unnamed: LED31.2 (DOUT), LED32.4 (DIN)
unnamed: LED32.2 (DOUT), LED33.4 (DIN)
unnamed: LED33.2 (DOUT), LED34.4 (DIN)
unnamed: LED34.2 (DOUT), LED35.4 (DIN)
unnamed: LED35.2 (DOUT), LED36.4 (DIN)
unnamed: LED36.2 (DOUT), LED37.4 (DIN)
unnamed: LED37.2 (DOUT), LED38.4 (DIN)
unnamed: LED38.2 (DOUT), LED39.4 (DIN)
unnamed: LED39.2 (DOUT), LED40.4 (DIN)
unnamed: LED40.2 (DOUT), LED41.4 (DIN)
unnamed: LED41.2 (DOUT), LED42.4 (DIN)
unnamed: LED42.2 (DOUT), LED43.4 (DIN)
unnamed: LED43.2 (DOUT), LED67.4 (DIN)
unnamed: LED44.2 (DOUT), LED45.4 (DIN)
unnamed: LED45.2 (DOUT), LED46.4 (DIN)
unnamed: LED46.2 (DOUT), LED47.4 (DIN)
unnamed: LED47.2 (DOUT), LED48.4 (DIN)
unnamed: LED48.2 (DOUT), LED49.4 (DIN)
unnamed: LED49.2 (DOUT), LED50.4 (DIN)
unnamed: LED50.2 (DOUT), LED51.4 (DIN)
unnamed: LED51.2 (DOUT), LED52.4 (DIN)
unnamed: LED52.2 (DOUT), LED53.4 (DIN)
unnamed: LED53.2 (DOUT), LED54.4 (DIN)
unnamed: LED54.2 (DOUT), LED55.4 (DIN)
unnamed: LED55.2 (DOUT), LED56.4 (DIN)
unnamed: LED56.2 (DOUT), LED57.4 (DIN)
unnamed: LED57.2 (DOUT), LED68.4 (DIN)
unnamed: LED58.2 (DOUT), LED59.4 (DIN)
unnamed: LED59.2 (DOUT), LED60.4 (DIN)
unnamed: LED61.2 (DOUT), LED62.4 (DIN)
unnamed: LED62.2 (DOUT), LED63.4 (DIN)
unnamed: LED63.2 (DOUT), LED64.4 (DIN)
unnamed: LED64.2 (DOUT), LED65.4 (DIN)
unnamed: LED65.2 (DOUT), LED66.4 (DIN)
RGB: LED60.2 (DOUT), LED61.4 (DIN); also elsewhere on the board
Row 1.2: LED14.2 (DOUT), LED15.4 (DIN)
Row 2.3: LED28.2 (DOUT), LED30.4 (DIN)
Row 3.4: LED44.4 (DIN), LED67.2 (DOUT)
Row 4.5: LED58.4 (DIN), LED68.2 (DOUT)

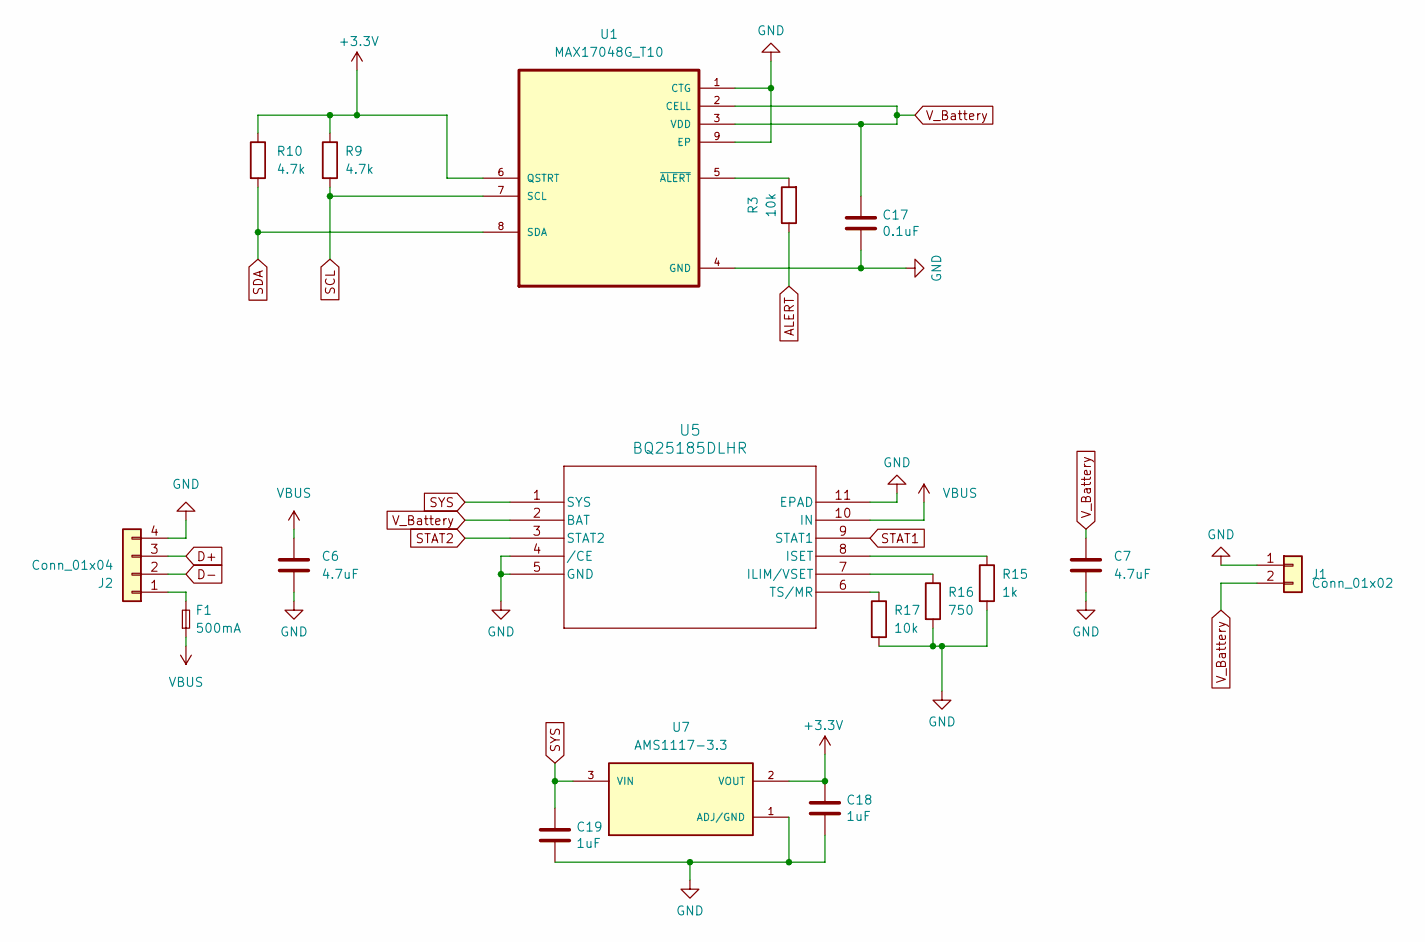
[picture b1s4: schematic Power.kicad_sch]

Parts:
C6, C7: 4.7uF; CAPC1005X55N
C17: 0.1uF; CAPC1005X55N; LCSC Part # C49678
C18, C19: 1uF; CAPC1005X55N; LCSC Part # C49678
F1: 500mA; Fuse_0603_1608Metric
J1: Conn_01x02; JST_PH_S2B-PH-SM4-TB_1x02-1MP_P2.00mm_Horizontal
J2: Conn_01x04; JST_SH_SM04B-SRSS-TB_1x04-1MP_P1.00mm_Horizontal
R3, R17: 10k; RESC1005X40N
R9, R10: 4.7k; RESC1005X40N
R15: 1k; RESC1005X40N
R16: 750; RESC1005X40N
U1: MAX17048G_T10; SON50P200X200X80-9N
U5: BQ25185DLHR; WSON10_DLH_TEX
U7: AMS1117-3.3; SOT229P700X180-4N; PARTREV NA

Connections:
+3.3V: C18.1, R9.1, R10.1, U1.6 (QSTRT), U7.2 (VOUT), U7.4; also elsewhere on the board
ALERT: R3.1; also elsewhere on the board
D+: J2.3; also elsewhere on the board
D-: J2.2; also elsewhere on the board
GND: C6.2, C7.2, C17.2, C18.2, C19.2, J1.1, J2.4, R15.2, R16.2, R17.2, U1.1 (CTG), U1.4 (GND), U1.9 (EP), U5.4 (/CE), U5.5 (GND), U5.11 (EPAD), U7.1 (ADJ/GND); also elsewhere on the board
unnamed: F1.2, J2.1
unnamed: R3.2, U1.5 (~ALERT)
unnamed: R16.1, U5.7 (ILIM/VSET)
unnamed: R15.1, U5.8 (ISET)
unnamed: R17.1, U5.6 (TS/MR)
SCL: R9.2, U1.7 (SCL); also elsewhere on the board
SDA: R10.2, U1.8 (SDA); also elsewhere on the board
STAT1: U5.9 (STAT1); also elsewhere on the board
STAT2: U5.3 (STAT2); also elsewhere on the board
SYS: C19.1, U5.1 (SYS), U7.3 (VIN)
VBUS: C6.1, F1.1, U5.10 (IN); also elsewhere on the board
V_Battery: C7.1, C17.1, J1.2, U1.2 (CELL), U1.3 (VDD), U5.2 (BAT)
